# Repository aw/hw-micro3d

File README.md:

# μ3D

### RatRig V-Core 3 EVA wiring over RJ45

A toolboard that mounts on a 3D printer hotend assembly to enable wiring over RJ45.

| | | |
| :----: | :----: | :----: |
|  |  |  |
| [Buy on Tindie](https://www.tindie.com/products/24538/) | [OSHW Certification](https://certification.oshwa.org/jp000011.html) | [Hackaday.io Project](https://hackaday.io/project/180918-3d-ratrig-v-core-3-eva-wiring-over-rj45) |

# Documentation

See the detailed documentation in the [docs/](docs/) directory:

  * [EXPLAIN](docs/EXPLAIN.md): learn the story behind this PCB, safety information, and OSHW
  * [HOWTO](docs/HOWTO.md): more detailed information on testing and wiring patterns
  * [REFERENCE](docs/REFERENCE.md): learn about the pinouts, trace widths, and other technical information
  * [TUTORIALS](docs/TUTORIALS.md): a quick guide to **get started** using this module

**Updated PCB v.2 now supports hotend heater cartridge, thermistor, and PWM fan.**

These instructions are for the **PCB v.2**. Please [click here to read instructions for PCB v.1](https://github.com/aw/hw-micro3d/releases/tag/v1).

**Note:** **PCB v.1 is not compatible with PCB v.2** due to the rerouted traces/wiring.

# Features

  * Form factor 80mm x 41mm
  * Lead-free, RoHS compliant
  * PCB traces are 0.5mm and can support at most 1A of current
  * High-current PCB traces are 3.0mm and can support at most 3.9A of current (2A tested)
  * Grounded M3 mounting holes connected to GND pins
  * Easy to source off-the-shelf through-hole components
  * Simple passive design draws 0mA current when no devices are connected

# Getting started

Click here to read the [tutorials](docs/TUTORIALS.md) quick guide to **get started**.

**DISCLAIMER: We are not responsible for accidents or problems caused by your use or misuse of these modules.**

# Notice

Usage of the logos and marks below are in no way an endorsement by their copyright and trademark owners.

* The Tindie and Hackaday logos are _Copyright © 2013, Supply Frame, Inc. All rights reserved._
* The OSHWA certification mark is _Trademark ™ 2018, the Open Source Hardware Association._

# License

μ3D: RatRig V-Core 3 EVA wiring over RJ45 and documentation © 2021 by [Alexander Williams](https://a1w.ca/) is licensed under [_CC BY-SA 4.0_ (Attribution-ShareAlike 4.0 International)](https://creativecommons.org/licenses/by-sa/4.0/).

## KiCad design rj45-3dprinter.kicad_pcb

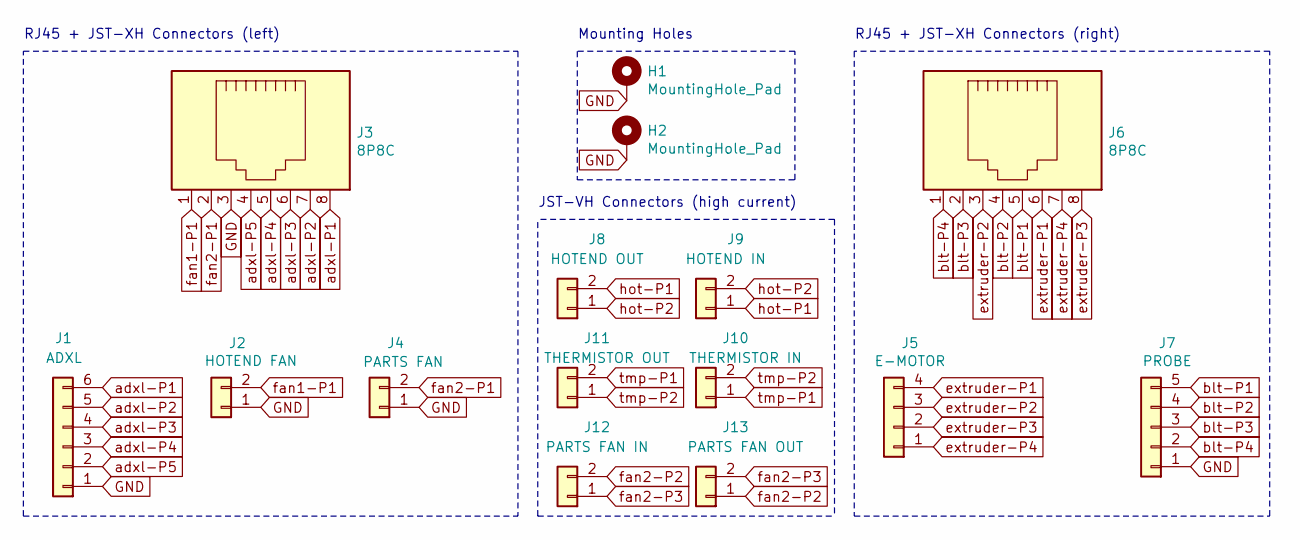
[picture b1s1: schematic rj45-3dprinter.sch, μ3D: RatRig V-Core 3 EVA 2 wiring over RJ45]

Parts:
H1, H2: MountingHole_Pad; MountingHole_3.2mm_M3_Pad_Via
J1: ADXL; JST_XH_B6B-XH-A_1x06_P2.50mm_Vertical
J2: HOTEND FAN; JST_XH_B2B-XH-A_1x02_P2.50mm_Vertical
J3, J6: 8P8C; RJ45_Amphenol_54602-x08_Horizontal_v02
J4: PARTS FAN; JST_XH_B2B-XH-A_1x02_P2.50mm_Vertical
J5: E-MOTOR; JST_XH_B4B-XH-A_1x04_P2.50mm_Vertical
J7: PROBE; JST_XH_B5B-XH-A_1x05_P2.50mm_Vertical
J8: HOTEND OUT; JST_VH_B2P-VH-FB-B_1x02_P3.96mm_Vertical
J9: HOTEND IN; JST_VH_B2P-VH-FB-B_1x02_P3.96mm_Vertical
J10: THERMISTOR IN; JST_VH_B2P-VH-FB-B_1x02_P3.96mm_Vertical
J11: THERMISTOR OUT; JST_VH_B2P-VH-FB-B_1x02_P3.96mm_Vertical
J12: PARTS FAN IN; JST_VH_B2P-VH-FB-B_1x02_P3.96mm_Vertical
J13: PARTS FAN OUT; JST_VH_B2P-VH-FB-B_1x02_P3.96mm_Vertical

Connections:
GND: H1.1, H2.1, J1.1, J2.1, J3.3, J4.1, J7.1
adxl-P1: J1.6, J3.8
adxl-P2: J1.5, J3.7
adxl-P3: J1.4, J3.6
adxl-P4: J1.3, J3.5
adxl-P5: J1.2, J3.4
blt-P1: J6.5, J7.5
blt-P2: J6.4, J7.4
blt-P3: J6.2, J7.3
blt-P4: J6.1, J7.2
extruder-P1: J5.4, J6.6
extruder-P2: J5.3, J6.3
extruder-P3: J5.2, J6.8
extruder-P4: J5.1, J6.7
fan1-P1: J2.2, J3.1
fan2-P1: J3.2, J4.2
fan2-P2: J12.2, J13.1
fan2-P3: J12.1, J13.2
hot-P1: J8.2, J9.1
hot-P2: J8.1, J9.2
tmp-P1: J10.1, J11.2
tmp-P2: J10.2, J11.1

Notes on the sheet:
Mounting Holes
RJ45 + JST-XH Connectors (left)
RJ45 + JST-XH Connectors (right)
JST-VH Connectors (high current)

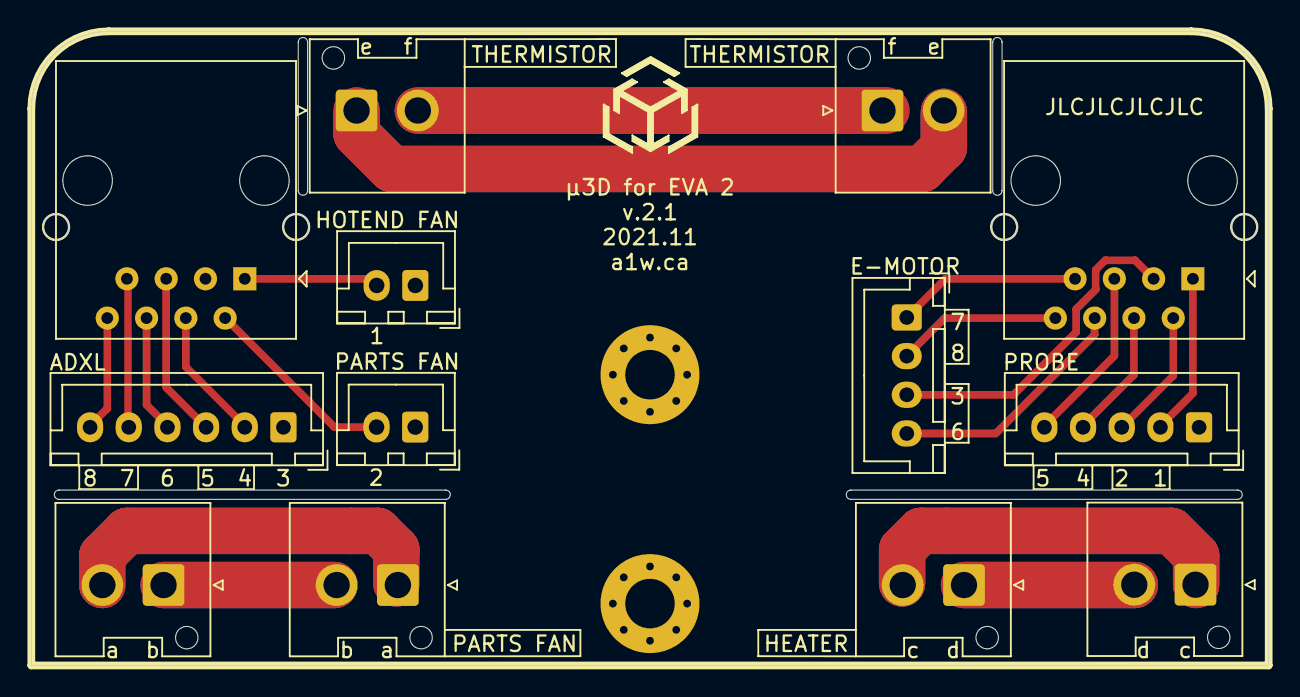
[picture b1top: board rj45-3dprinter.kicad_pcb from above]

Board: 2 copper layers, 80.0 x 41.0 mm, 15 parts (0 on the bottom side), 22 nets.

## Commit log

2021-08-15 Add design files
2021-08-15 Add schematic and pinout
2021-08-15 Add README and datasheets
2021-08-15 Add image of bare PCBs
2021-11-24 Update PCB for hotend (high-current) components
2021-11-24 Add OSHWA certification mark
2021-11-24 Update OSHWA certification mark
2021-11-27 Add detailed documentation in 'docs/' and update README
2021-11-29 Fix invalid HOWTO link in README.md
2021-12-08 Fix minor typos
2022-03-21 Add alternate wiring scheme to documentation
2022-03-21 Add alternate 1 and 2 charts
2022-05-11 Update documentation note about 2-wire fans and thermistor.
    Thanks to Mitsuma for the heads-up
2022-05-14 Add warning about speed control of a 2-wire fan

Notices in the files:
rj45-3dprinter.sch:
License: CC BY-SA 4.0
